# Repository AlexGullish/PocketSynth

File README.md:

# PocketSynth

PocketSynth is a small DIY electronic instrument built around a classic Arduino Nano. It uses eight push buttons to play notes and a ninth button to cycle between three octave settings. The firmware can mix up to four notes at once, creating simple polyphonic sound through a passive piezo buzzer.

## Features
- Eight note buttons for a C-major scale from C4 to C5.
- Four-note polyphony: up to four notes can sound simultaneously.
- Three octave settings: low, normal, and high, selected with the octave button.
- Button debouncing to help prevent accidental repeated state changes.
- Passive piezo output driven by timer-based waveform generation.

## Controls
Playing notes
Press any note button to play its assigned note. Up to four pressed note buttons are processed at once. If more than four note buttons are held, the firmware uses the first four pressed keys in the sketch's pin-array order (D2 through D9); additional held keys are ignored until one of those selected keys is released.

## Changing octaves
Press the button connected to D11 to cycle through the octave settings:
1. Normal — the frequencies listed in the pinout table
2. High — frequencies doubled
3. Low — frequencies halved
4. Then back to Normal
The initial setting after startup is Normal.

An enclosure was also build to house the PCB

## BOM

| Item             | Qty | Supplier     | Cost/item | Total Cost | link                                                                                                                                                                                                                                                                                                                                                                                                                                                                                                       |
|------------------|-----|--------------|-----------|------------|------------------------------------------------------------------------------------------------------------------------------------------------------------------------------------------------------------------------------------------------------------------------------------------------------------------------------------------------------------------------------------------------------------------------------------------------------------------------------------------------------------|
| PCB              | 1   | JLCPCB       | $8.10     | $8.10      | https://cart.jlcpcb.com/quote?stencilLayer=2&stencilWidth=100&stencilLength=100&stencilCounts=5&plateType=1&spm=Jlcpcb.Homepage.1010                                                                                                                                                                                                                                                                                                                                                                       |
| Piezo Buzzer     | 1   | BastelGarage | $1.82     | $1.82      | https://www.bastelgarage.ch/piezo-buzzer-summer-aktiv?search=piezo                                                                                                                                                                                                                                                                                                                                                                                                                                         |
| Arduino Nano     | 1   | Amazon       | $11.99    | $11.99     | https://www.amazon.com/LUIRSAY-2Pcs-ATmega328P-Microcontroller-Compatible/dp/B0F1FQMNXM?crid=2W5GSQBC3HIJB&dib=eyJ2IjoiMSJ9.lGGUnkwyBAbnKti6S6SwYP2c6x-UGxlnKYzt2PNPgECSCdozHIAZ0OdamOZFqWbMvz8xpCRb1nKdGy6rfSHLUQPwaf3XGjoTjaAqPtBrrFQidVU9YVl90a602_HgnH4SrCyEkPTpDEKaLqP4j7S698Nc5fnB4vXDp_cE3KJylL8MgglIj20uxDazyTZKai4Y2EyphATkz1YSZvYsvpz0hkyqVcIGBWoc2mZFOu4FiWo.LpxEV_klTvgMHI9_awVb41E-o6UUeTSc5VZ7_uwAcRE&dib_tag=se&keywords=arduino+nano&qid=1792962564&sprefix=arduino+nan%2Caps%2C237&sr=8-3 |
| Switches         | 9   | BerryBase    | $1.12     | $10.08     | https://www.berrybase.ch/en/cherry-mx-blue-pushbutton-module-pcb-fixing-pin                                                                                                                                                                                                                                                                                                                                                                                                                                |
| Estimated total  |     |              |           | $31.99     |                                                                                                                                                                                                                                                                                                                                                                                                                                                                                                            |

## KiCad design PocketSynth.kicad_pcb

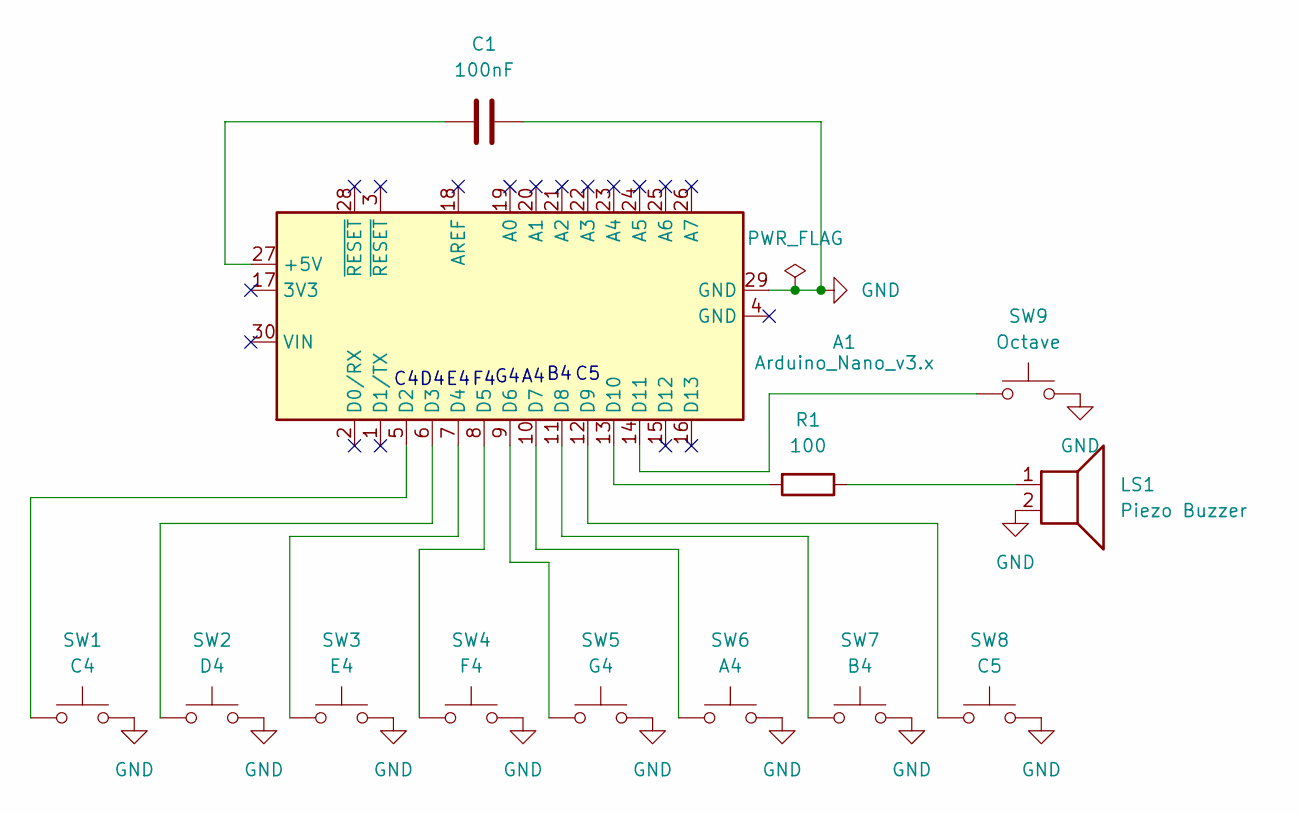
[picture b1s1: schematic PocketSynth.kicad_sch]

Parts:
A1: Arduino_Nano_v3.x; Arduino_Nano
C1: 100nF; C_0805_2012Metric
LS1: Piezo Buzzer; Buzzer_12x9.5RM7.6
R1: 100; R_0805_2012Metric
SW1: C4; SW_Cherry_MX_1.00u_PCB
SW2: D4; SW_Cherry_MX_1.00u_PCB
SW3: E4; SW_Cherry_MX_1.00u_PCB
SW4: F4; SW_Cherry_MX_1.00u_PCB
SW5: G4; SW_Cherry_MX_1.00u_PCB
SW6: A4; SW_Cherry_MX_1.00u_PCB
SW7: B4; SW_Cherry_MX_1.00u_PCB
SW8: C5; SW_Cherry_MX_1.00u_PCB
SW9: Octave; SW_Cherry_MX_1.00u_PCB

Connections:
GND: A1.29 (GND), C1.2, LS1.2, SW1.2, SW2.2, SW3.2, SW4.2, SW5.2, SW6.2, SW7.2, SW8.2, SW9.2
unnamed: A1.27 (+5V), C1.1
unnamed: A1.5 (D2), SW1.1
unnamed: A1.6 (D3), SW2.1
unnamed: A1.7 (D4), SW3.1
unnamed: A1.8 (D5), SW4.1
unnamed: A1.9 (D6), SW5.1
unnamed: A1.10 (D7), SW6.1
unnamed: A1.11 (D8), SW7.1
unnamed: A1.12 (D9), SW8.1
unnamed: A1.13 (D10), R1.2
unnamed: A1.14 (D11), SW9.1
unnamed: LS1.1, R1.1

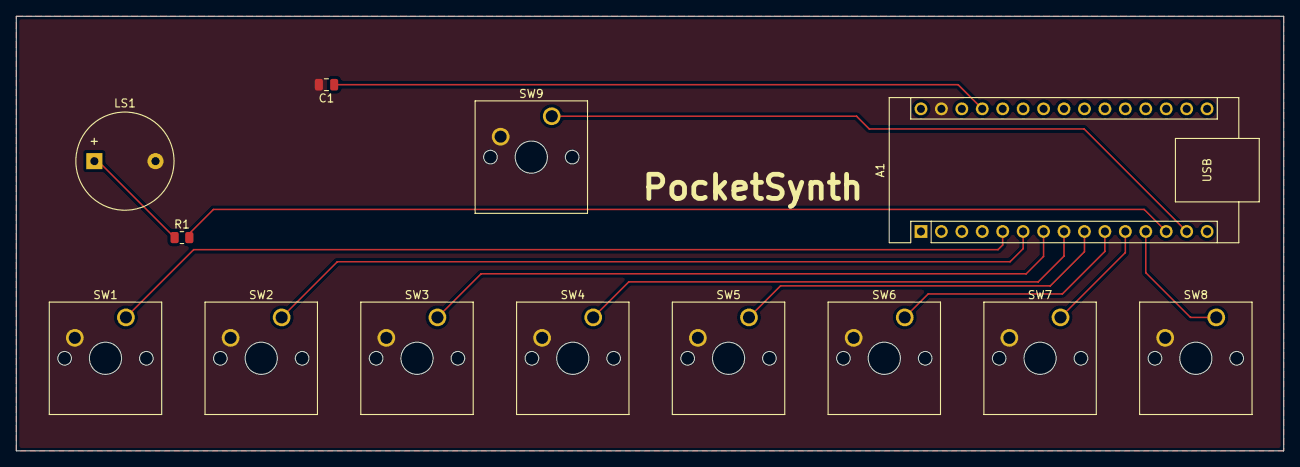
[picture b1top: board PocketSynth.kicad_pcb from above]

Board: 2 copper layers, 157.5 x 54.0 mm, 13 parts (0 on the bottom side), 13 nets.
